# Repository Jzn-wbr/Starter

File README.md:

<div align="center">

# Réveil

### Un réveil qui vous aide vraiment à sortir du lit.

Un système de réveil connecté qui combine une station audio, un bracelet de mouvement et une application mobile pour transformer le réveil en un vrai départ de journée.

**Projet personnel · Version finale du produit**

</div>

## L’idée

Les réveils classiques s’arrêtent d’une pression sur un bouton. Celui-ci est pensé pour rendre le retour au sommeil beaucoup plus difficile : l’alarme démarre à l’heure choisie et ne se calme qu’après avoir détecté une activité réelle grâce au bracelet.

Pas de bouton snooze. Pas de négociation avec soi-même à 7 h 30.

## Une expérience en trois éléments

| | Rôle |
| --- | --- |
| **La station** | Le centre du système : elle déclenche l’alarme, diffuse la musique et supervise le réveil. |
| **Le bracelet** | Il détecte les mouvements et confirme que la journée a réellement commencé. |
| **L’application** | Elle permet de choisir l’heure, la musique et de vérifier que les appareils sont prêts. |

## Comment ça marche

1. Choisissez une heure et votre son de réveil dans l’application.
2. La station se prépare pour le lendemain et synchronise la configuration.
3. À l’heure prévue, la musique démarre sur la station.
4. Le bracelet mesure votre activité pendant une fenêtre dédiée.
5. Quand le mouvement est confirmé, le réveil peut enfin s’arrêter.

L’objectif : remplacer le réflexe « encore cinq minutes » par un réveil plus franc, plus personnel et plus difficile à ignorer.

## En images

<div align="center">

</div>

## Une base ouverte pour un objet complet

Ce dépôt rassemble l’application mobile, le firmware de la station, le firmware du bracelet, les schémas électroniques et la documentation du système. Il présente la version finale du produit, pensée comme un réveil fiable, agréable à utiliser et réellement efficace.

> Le système est conçu pour un usage personnel. Les choix techniques et les fonctionnalités peuvent encore évoluer.

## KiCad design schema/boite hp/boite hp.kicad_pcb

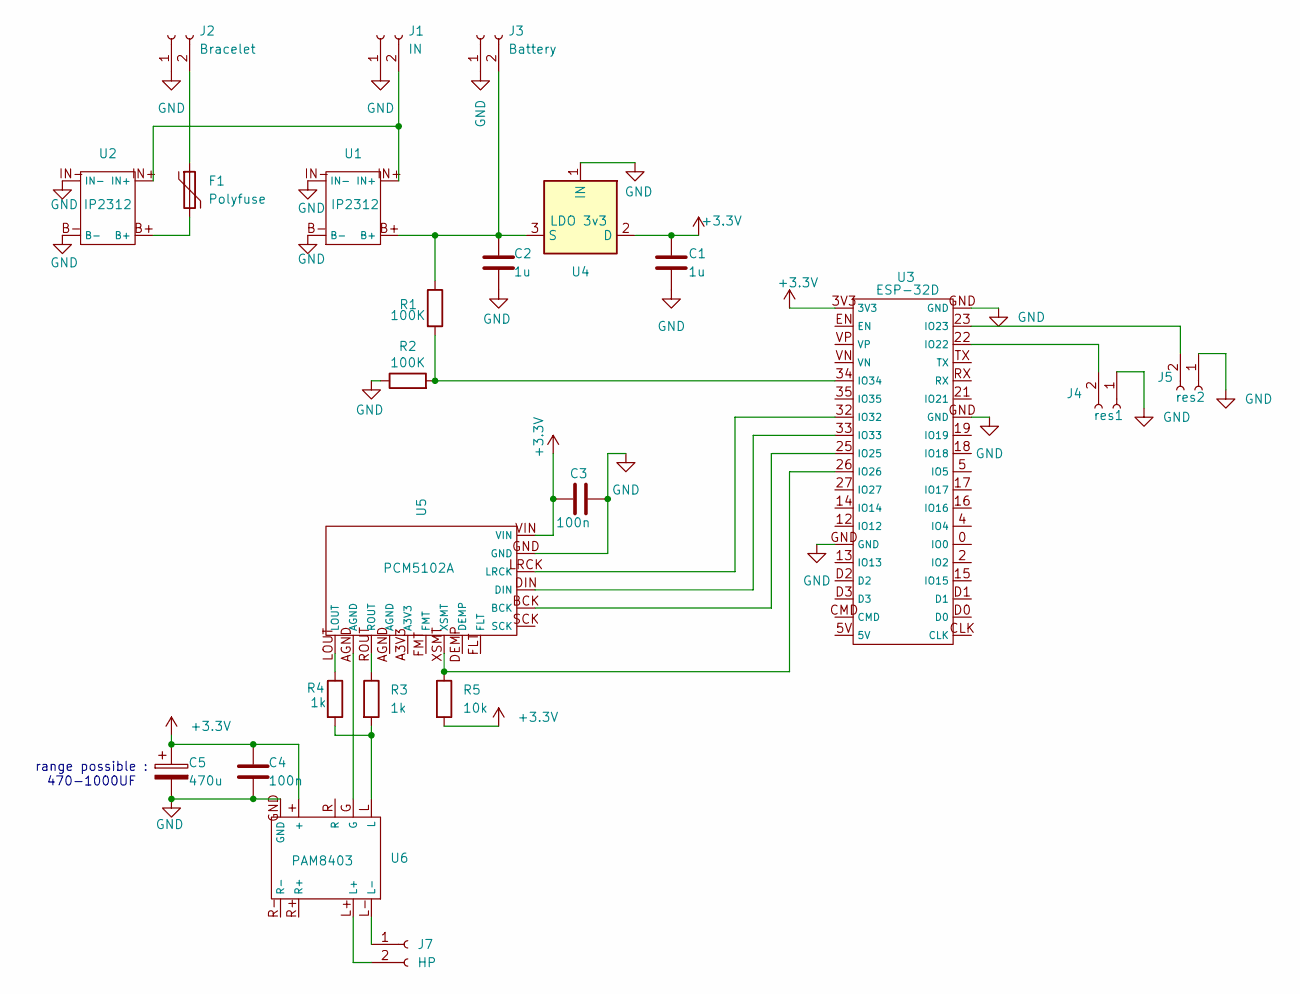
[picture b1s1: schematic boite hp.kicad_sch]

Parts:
C1, C2: 1u; C_0805_2012Metric
C3, C4: 100n; C_0805_2012Metric
C5: 470u; CP_Radial_D8.0mm_P3.50mm
F1: Polyfuse; C_Disc_D5.0mm_W2.5mm_P5.00mm
J1: IN; JST_PH_B2B-PH-K_1x02_P2.00mm_Vertical
J2: Bracelet; JST_PH_B2B-PH-K_1x02_P2.00mm_Vertical
J3: Battery; JST_PH_B2B-PH-K_1x02_P2.00mm_Vertical
J4: res1; JST_PH_B2B-PH-K_1x02_P2.00mm_Vertical
J5: res2; JST_PH_B2B-PH-K_1x02_P2.00mm_Vertical
J7: HP; JST_PH_B2B-PH-K_1x02_P2.00mm_Vertical
R1, R2: 100K; R_1206_3216Metric
R3, R4: 1k; R_1206_3216Metric
R5: 10k; R_1206_3216Metric
U1, U2: IP2312
U3: ESP-32D; ESP-32D devkit
U4: LDO 3v3; SOT-223-3_TabPin2
U5: PCM5102A; PCM5102A Module
U6: PAM8403; PAM8403 Module

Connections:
+3.3V: C1.1, C3.1, C4.1, C5.1, R5.2, U3.3V3, U4.2 (D), U5.VIN, U6.+
GND: C1.2, C2.2, C3.2, C4.2, C5.2, J1.1, J2.1, J3.1, J4.1, J5.1, R2.1, U1.B-, U1.IN-, U2.B-, U2.IN-, U3.GND, U4.1 (IN), U5.GND, U6.GND
unnamed: F1.2, U2.B+
unnamed: J1.2, U1.IN+, U2.IN+
unnamed: F1.1, J2.2
unnamed: C2.1, J3.2, R1.1, U1.B+, U4.3 (S)
unnamed: J4.2, U3.22 (IO22)
unnamed: J5.2, U3.23 (IO23)
unnamed: J7.1, U6.L-
unnamed: J7.2, U6.L+
unnamed: R3.1, U5.ROUT
unnamed: R3.2, R4.2, U6.L
unnamed: R4.1, U5.LOUT
unnamed: U3.25 (IO25), U5.BCK
unnamed: R5.1, U3.26 (IO26), U5.XSMT
unnamed: U3.32 (IO32), U5.LRCK
unnamed: U3.33 (IO33), U5.DIN
unnamed: R1.2, R2.2, U3.34 (IO34)
unnamed: U5.AGND, U6.G

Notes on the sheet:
range possible : 470-1000UF

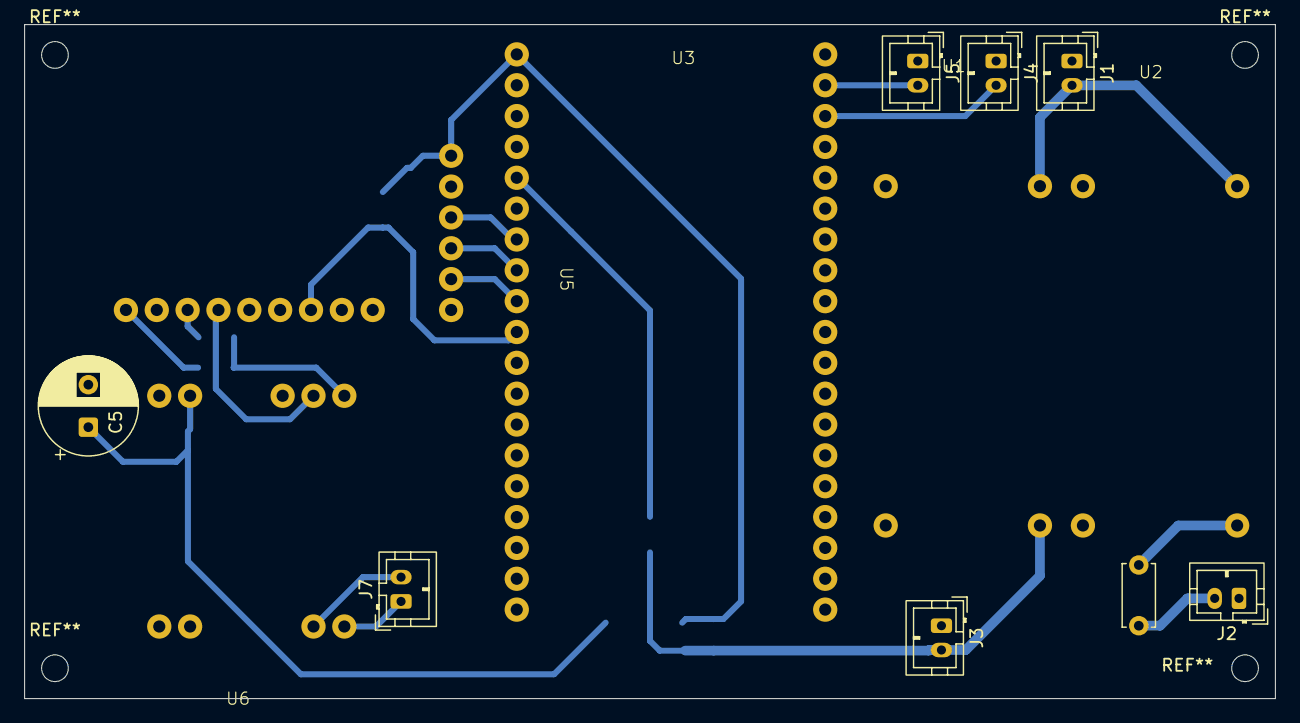
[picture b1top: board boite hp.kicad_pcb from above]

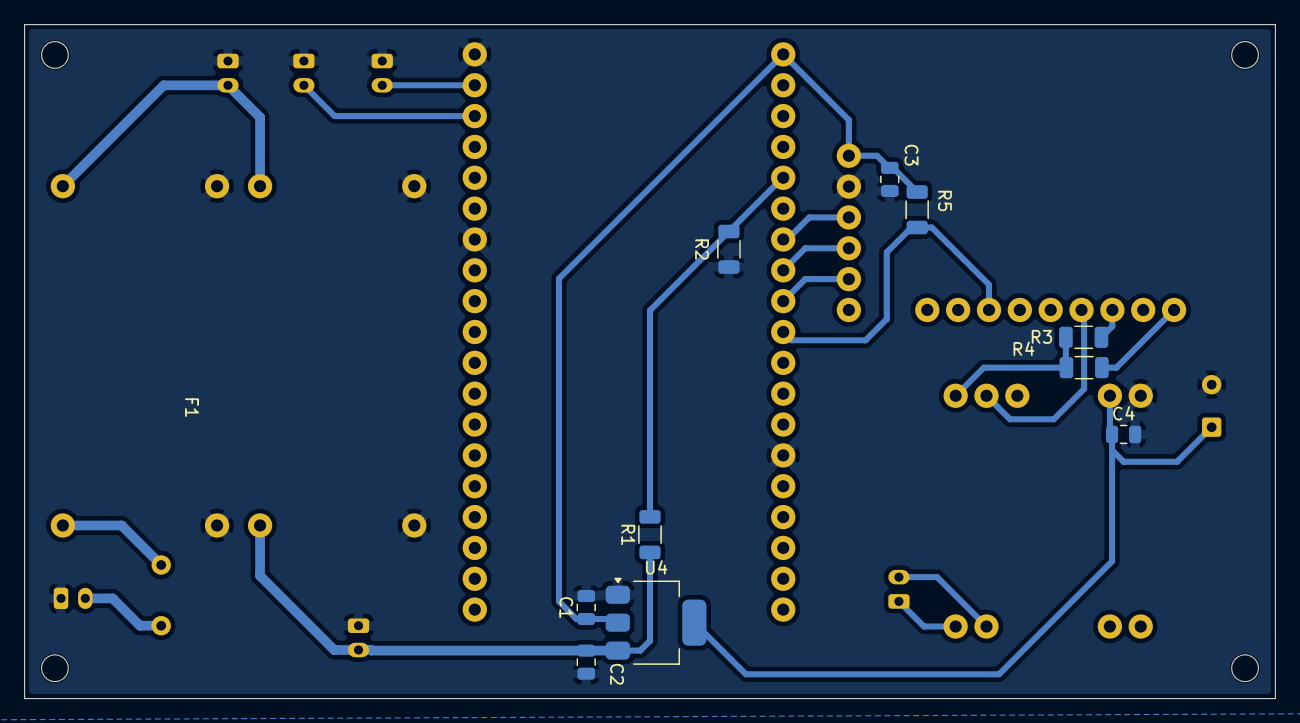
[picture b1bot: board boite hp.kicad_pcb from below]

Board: 2 copper layers, 103.0 x 55.5 mm, 23 parts (10 on the bottom side), 19 nets.

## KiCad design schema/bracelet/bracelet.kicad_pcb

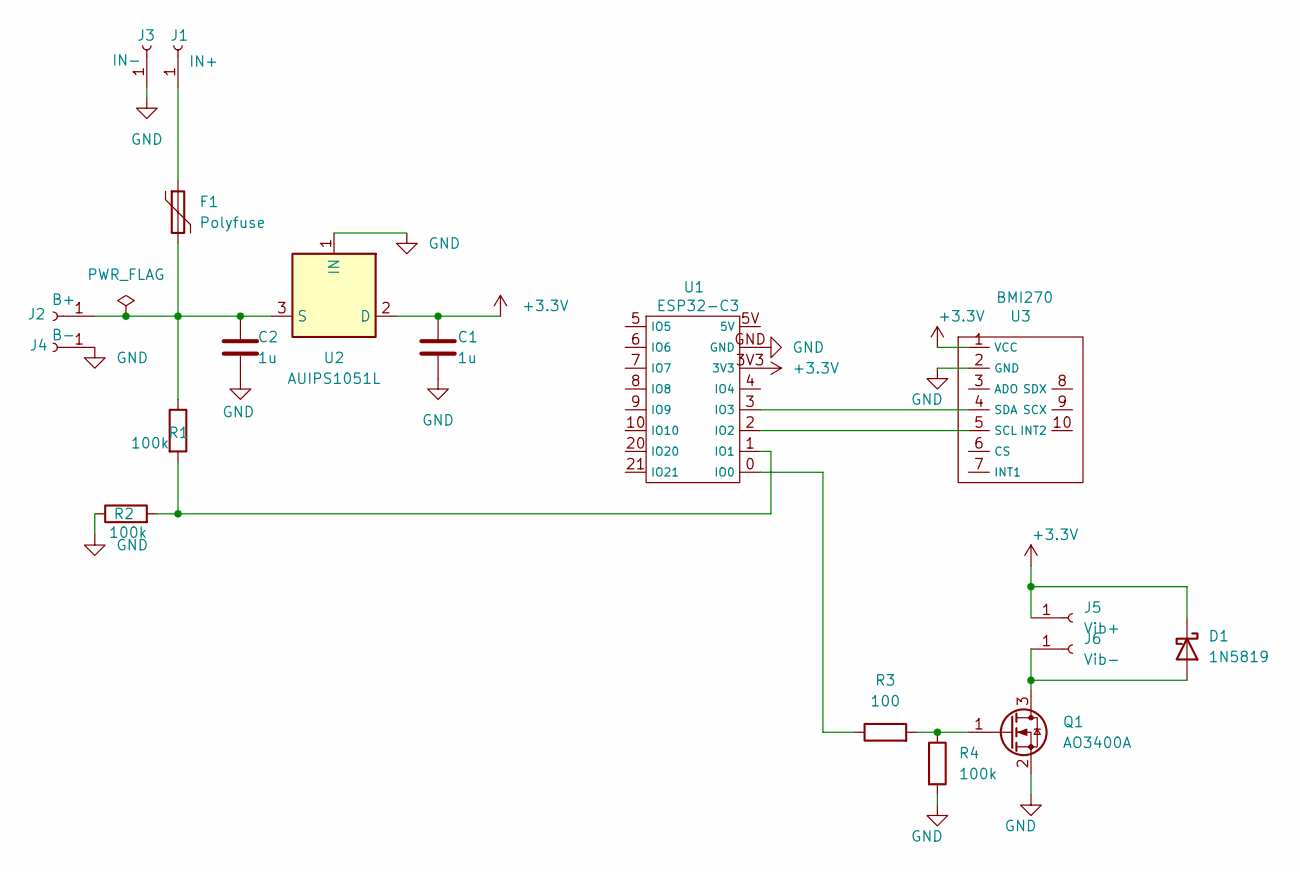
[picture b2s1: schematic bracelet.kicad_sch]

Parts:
C1, C2: 1u; C_0805_2012Metric
D1: 1N5819; D_SMA
F1: Polyfuse; C_Disc_D5.0mm_W2.5mm_P5.00mm
J1: IN+; SolderWirePad_1x01_SMD_2x4mm
J2: B+; SolderWirePad_1x01_SMD_2x4mm
J3: IN-; SolderWirePad_1x01_SMD_2x4mm
J4: B-; SolderWirePad_1x01_SMD_2x4mm
J5: Vib+; SolderWirePad_1x01_SMD_2x4mm
J6: Vib-; SolderWirePad_1x01_SMD_2x4mm
Q1: AO3400A; SOT-23
R1, R2, R4: 100k; R_1206_3216Metric
R3: 100; R_1206_3216Metric
U1: ESP32-C3; ESP32-C3 HW-466B
U2: AUIPS1051L; SOT-223-3_TabPin2
U3: BMI270; BMI270 module

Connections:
+3.3V: C1.1, D1.1 (K), J5.1 (Pin_1_1), U1.3V3, U2.2 (D), U3.1 (VCC)
GND: C1.2, C2.2, J3.1 (Pin_1_1), J4.1 (Pin_1_1), Q1.2 (S), R2.1, R4.2, U1.GND, U2.1 (IN), U3.2 (GND)
unnamed: D1.2 (A), J6.1 (Pin_1_1), Q1.3 (D)
unnamed: F1.1, J1.1 (Pin_1_1)
unnamed: C2.1, F1.2, J2.1 (Pin_1_1), R1.1, U2.3 (S)
unnamed: Q1.1 (G), R3.2, R4.1
unnamed: R3.1, U1.0 (IO0)
unnamed: R1.2, R2.2, U1.1 (IO1)
unnamed: U1.2 (IO2), U3.5 (SCL)
unnamed: U1.3 (IO3), U3.4 (SDA)

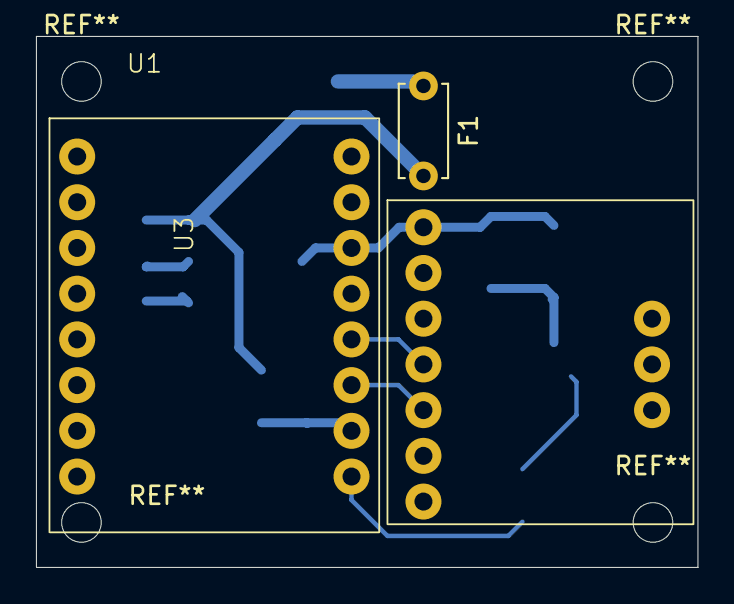
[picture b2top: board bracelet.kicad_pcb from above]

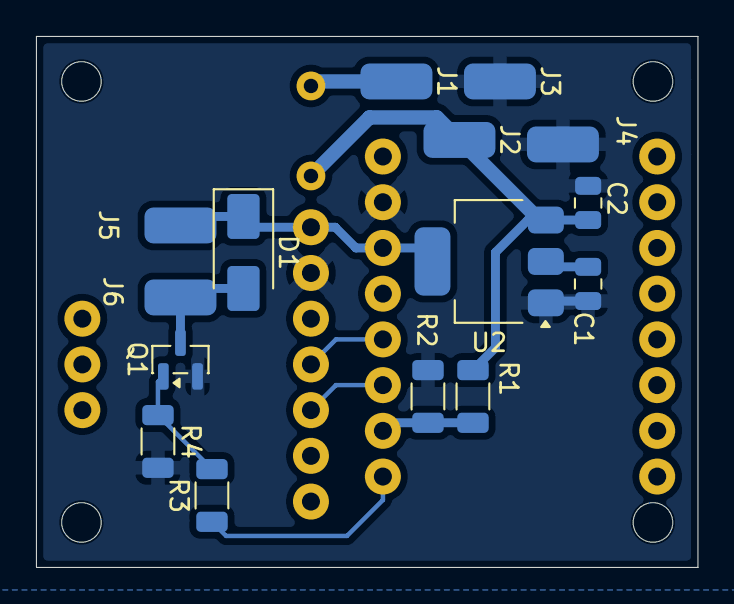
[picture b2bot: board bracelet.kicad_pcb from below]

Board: 2 copper layers, 36.8 x 29.5 mm, 18 parts (15 on the bottom side), 10 nets.

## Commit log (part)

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2026-04-30 Add project agent guides and architecture contracts
2026-04-30 Add UML documentation rules and app use cases
2026-04-30 Implement database schema
2026-04-30 Add schematic file for hp box
2026-05-03 Design bracelet PCB
2026-05-04 Add boite hp schema
2026-05-08 Update Architecture db
2026-05-08 PWA v1
2026-05-08 Reduce pooling to active window
2026-05-10 A lot
2026-05-10 Improve alarm UI clarity and status layout
2026-05-10 Improve alarm UI clarity and interactive time selection
2026-05-10 Improve alarm UI visibility and activation controls
2026-05-10 Refine mobile alarm UX with clearer time and status
2026-05-10 Update app UML for alarm controls
2026-05-10 Update alarm status and activity window behavior
